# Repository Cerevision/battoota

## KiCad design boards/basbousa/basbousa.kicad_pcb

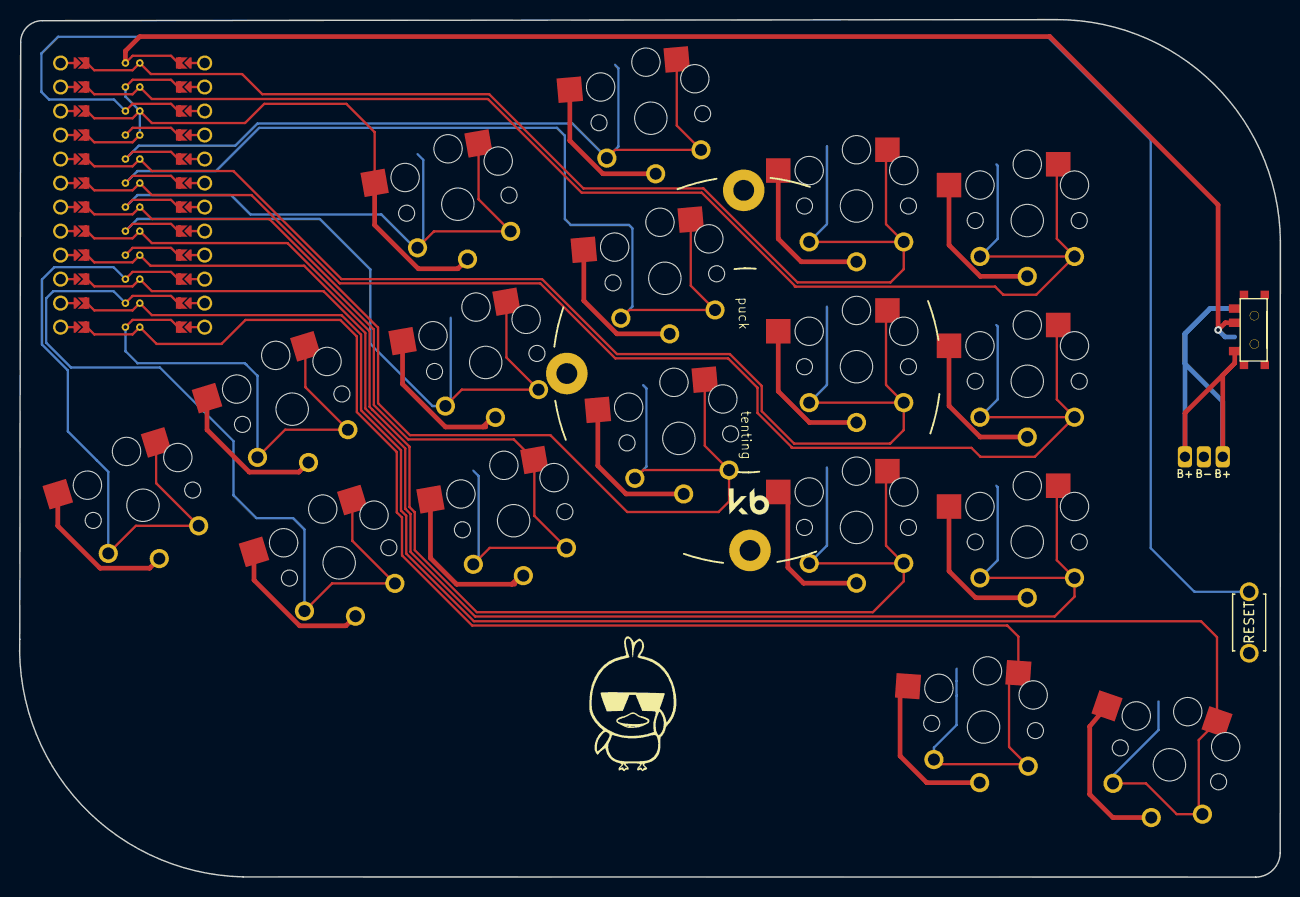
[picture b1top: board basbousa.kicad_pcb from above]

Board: 2 copper layers, 133.4 x 90.7 mm, 21 parts (0 on the bottom side), 3 nets.

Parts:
B1: ResetSW
PAD1: bat
S1, S3, S5, S7, S9, S11, S13, S15, S17, S19, S21, S23, S25, S27, S29, S31, S33: key
T1, T2: SPDT_C128955

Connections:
Braw: PAD1.1, T1.1, T2.1
GND: B1.2, PAD1.2, S1.2, S3.2, S5.2, S7.2, S9.2, S11.2, S13.2, S15.2, S17.2, S19.2, S21.2, S23.2, S25.2, S27.2, S29.2, S31.2, S33.2
RAW: T1.2, T2.2

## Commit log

2022-06-10 tighter basbousa
